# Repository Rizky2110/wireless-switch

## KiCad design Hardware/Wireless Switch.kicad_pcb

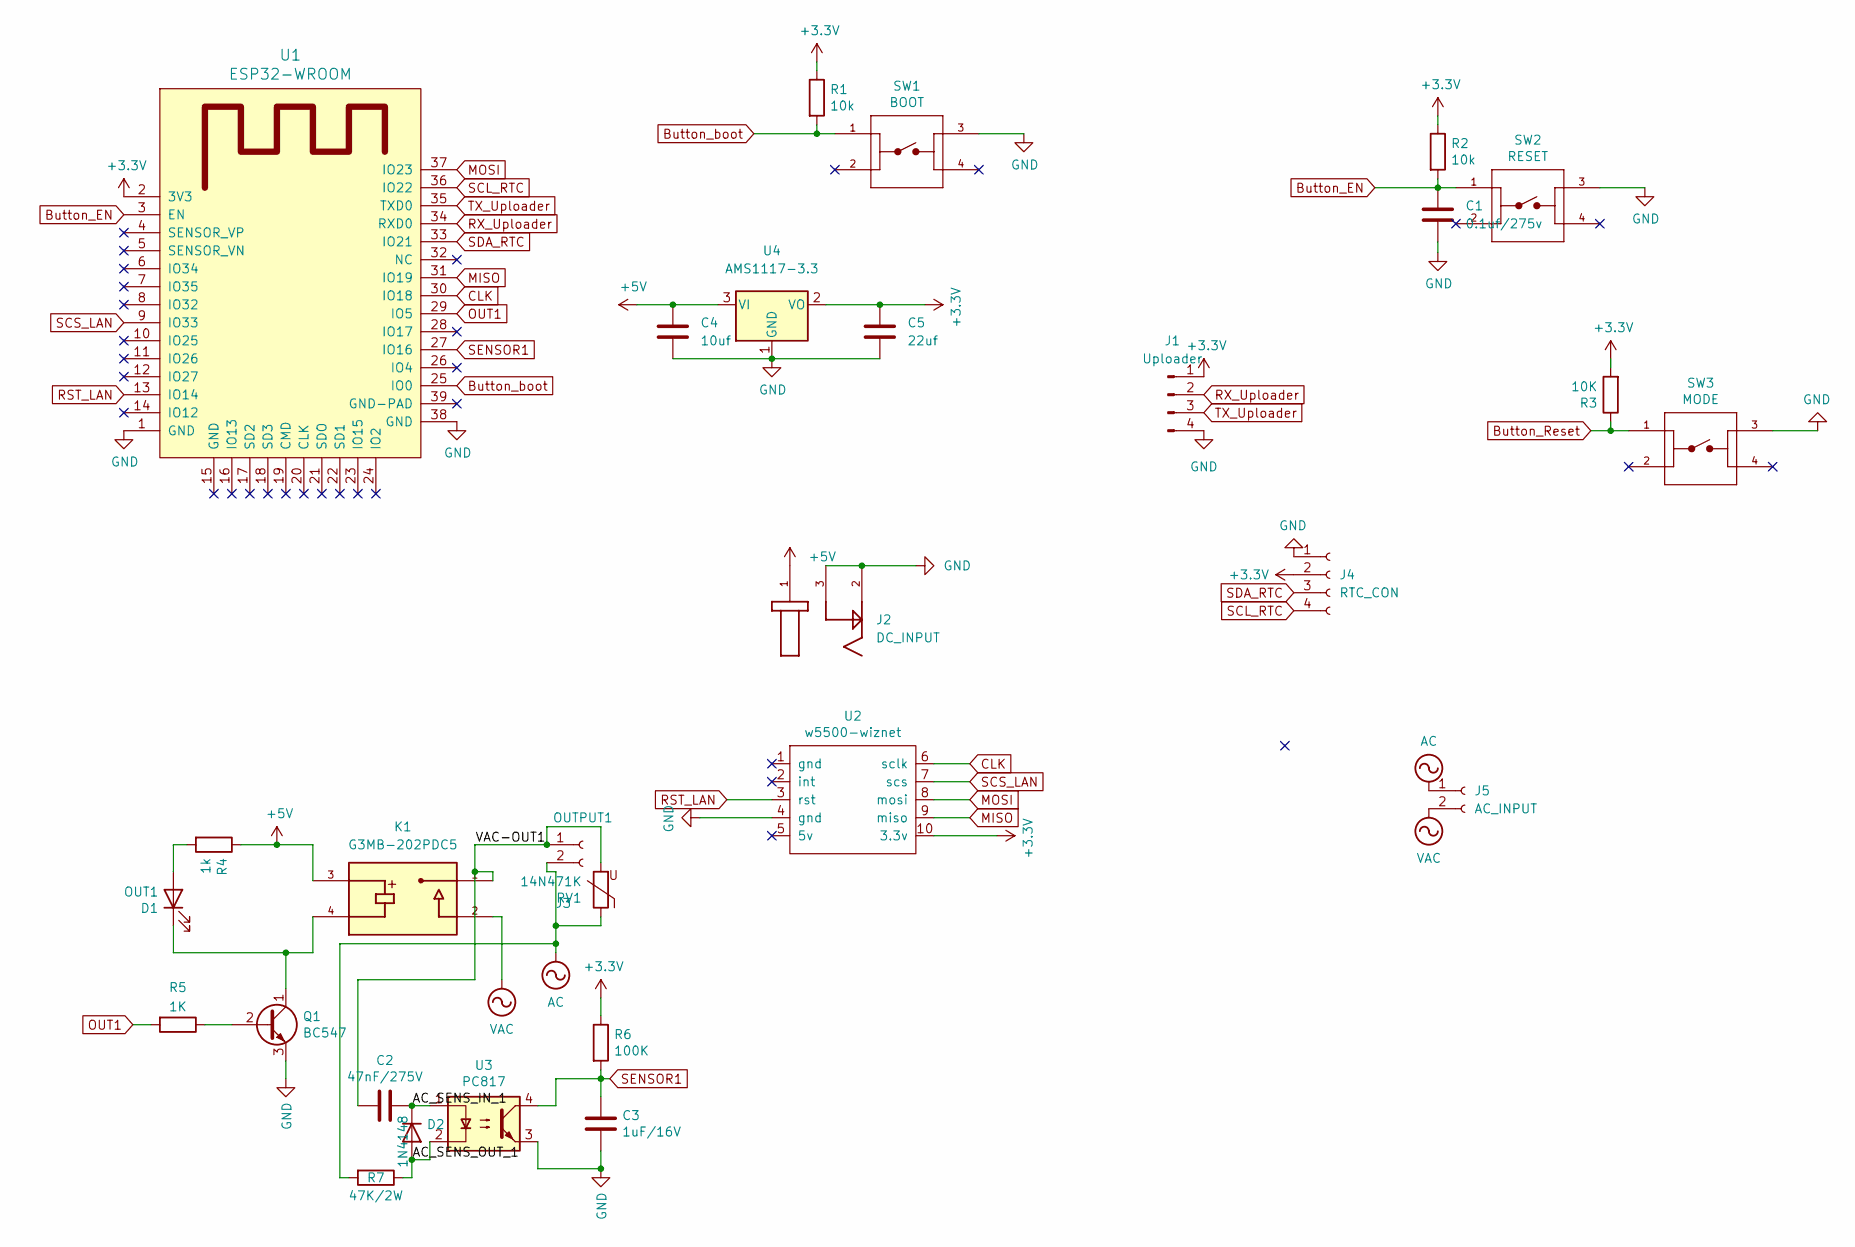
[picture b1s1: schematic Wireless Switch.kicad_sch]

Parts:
C1: 0.1uf/275v; C_Rect_L7.2mm_W2.5mm_P5.00mm_FKS2_FKP2_MKS2_MKP2
C2: 47nF/275V; C_Rect_L13.0mm_W5.0mm_P10.00mm_FKS3_FKP3_MKS4
C3: 1uF/16V; CP_Radial_Tantal_D5.0mm_P2.50mm
C4: 10uf; CP_Radial_Tantal_D5.0mm_P2.50mm
C5: 22uf; CP_Radial_Tantal_D5.0mm_P2.50mm
D1: OUT1; LED_D3.0.0mm
D2: 1N4148; D_5W_P10.16mm_Horizontal
J1: Uploader; PinHeader_1x04_P2.54mm_Vertical
J2: DC_INPUT; GCT_DCJ200-10-A-XX-X_REVA
J3: OUTPUT1; TerminalBlock_Wuerth_691311400102_P7.62mm
J4: RTC_CON; RTC_DS3231
J5: AC_INPUT; TerminalBlock_Wuerth_691311400102_P7.62mm
K1: G3MB-202PDC5; RELAY_G3MB-202PDC5_SSR; PARTREV J091-E1-1A
Q1: BC547; TO-92_Inline_Wide
R1, R2: 10k; R_0805_2012Metric_Pad1.20x1.40mm_HandSolder
R3: 10K; R_0805_2012Metric_Pad1.20x1.40mm_HandSolder
R4: 1k; R_0805_2012Metric_Pad1.20x1.40mm_HandSolder
R5: 1K; R_0805_2012Metric_Pad1.20x1.40mm_HandSolder
R6: 100K; R_0805_2012Metric_Pad1.20x1.40mm_HandSolder
R7: 47K/2W; R_Axial_DIN0516_L15.5mm_D5.0mm_P20.32mm_Horizontal
RV1: 14N471K; RV_Disc_D12mm_W7.1mm_P7.5mm
SW1: BOOT; TE_3-1825910-1
SW2: RESET; TE_3-1825910-1
SW3: MODE; TE_3-1825910-1
U1: ESP32-WROOM
U2: w5500-wiznet; ethernet-w5500-wiznet
U3: PC817; DIP-4_W7.62mm
U4: AMS1117-3.3; SOT-223-3_TabPin2

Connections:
+3V3: C5.1, J1.1, J4.2, R1.1, R2.1, R3.2, R6.1, U1.2 (3V3), U2.10 (3.3v), U4.2 (VO)
+5V: C4.1, J2.1, K1.3, R4.1, U4.3 (VI)
/AC_SENS_IN_1: C2.1, D2.1 (K), U3.1
/AC_SENS_OUT_1: D2.2 (A), R7.1, U3.2
/VAC-OUT1: C2.2, J3.1, K1.1, RV1.2
AC: J3.2, J5.1, R7.2, RV1.1
Button_EN: C1.1, R2.2, SW2.1, U1.3 (EN)
Button_Reset: R3.1, SW3.1
Button_boot: R1.2, SW1.1, U1.25 (IO0)
CLK: U1.30 (IO18), U2.6 (sclk)
GND: C1.2, C3.2, C4.2, C5.2, J1.4, J2.2, J2.3, J4.1, Q1.3 (E), SW1.3, SW2.3, SW3.3, U1.1 (GND), U1.38 (GND), U2.4 (gnd), U3.3, U4.1 (GND)
MISO: U1.31 (IO19), U2.9 (miso)
MOSI: U1.37 (IO23), U2.8 (mosi)
unnamed: D1.1 (K), K1.4, Q1.1 (C)
unnamed: D1.2 (A), R4.2
unnamed: Q1.2 (B), R5.1
OUT1: R5.2, U1.29 (IO5)
RST_LAN: U1.13 (IO14), U2.3 (rst)
RX_Uploader: J1.2, U1.34 (RXD0)
SCL_RTC: J4.4, U1.36 (IO22)
SCS_LAN: U1.9 (IO33), U2.7 (scs)
SDA_RTC: J4.3, U1.33 (IO21)
SENSOR1: C3.1, R6.2, U1.27 (IO16), U3.4
TX_Uploader: J1.3, U1.35 (TXD0)
VAC: J5.2, K1.2

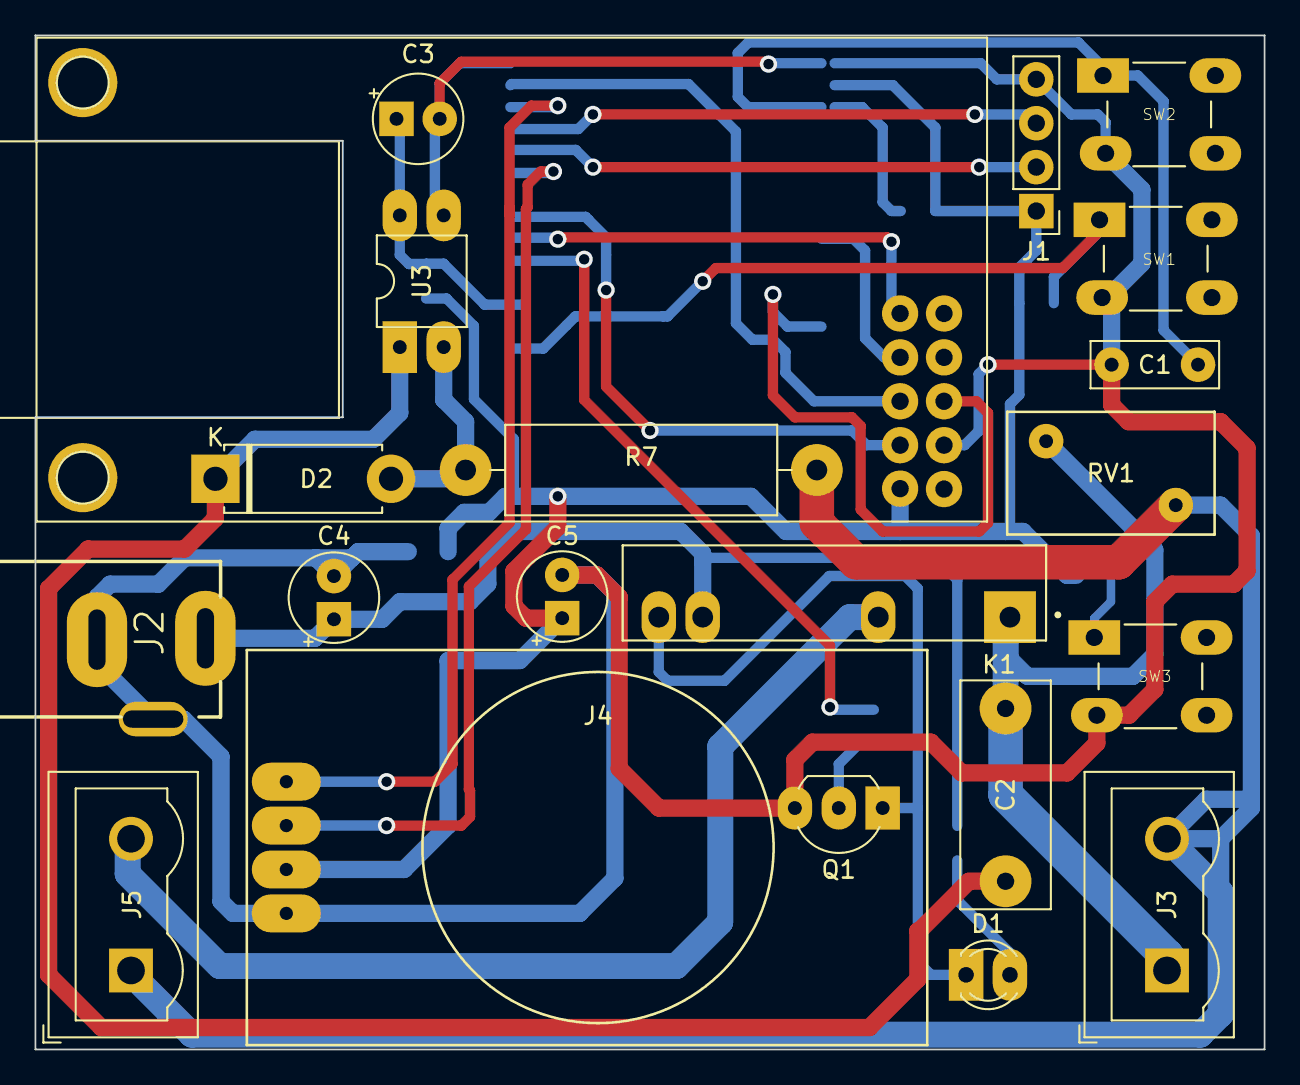
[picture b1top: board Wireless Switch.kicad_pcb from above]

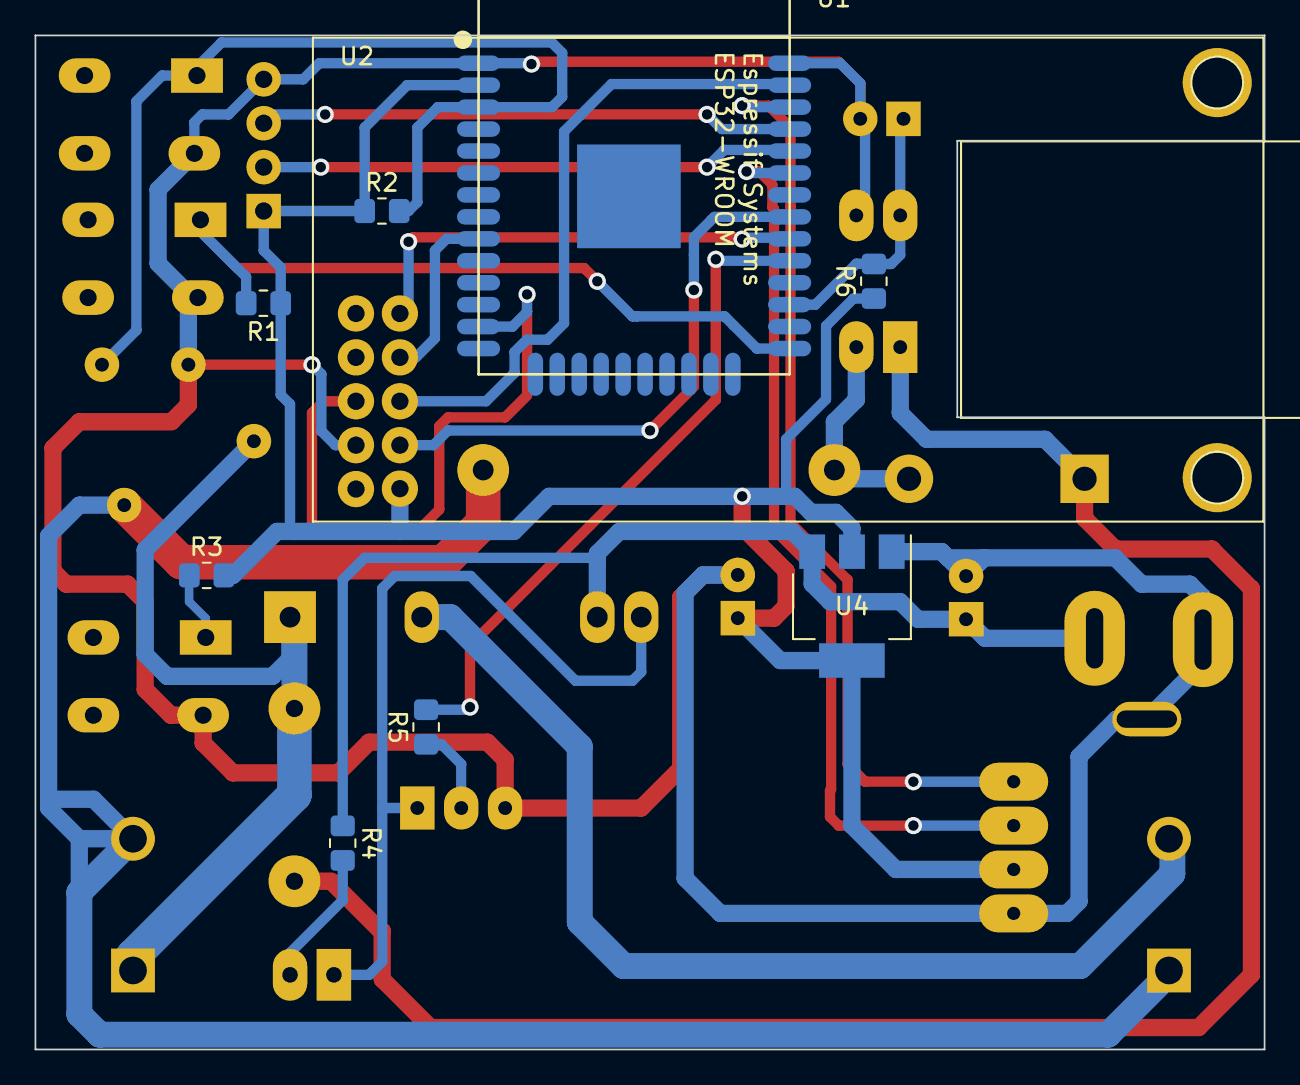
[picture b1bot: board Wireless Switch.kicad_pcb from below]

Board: 2 copper layers, 71.1 x 58.7 mm, 29 parts (9 on the bottom side), 25 nets.

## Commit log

2023-03-17 create schematic device
2023-03-17 Add firmware set up platform io
2023-03-20 route pcb
